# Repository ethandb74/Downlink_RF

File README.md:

# Downlink_RF
4-layer PCB LoRa Puck:

This is a usb powereed LoRA Transmitter made for long range comnmunication with a programmable OLED display. This project was built around the SX1262 Radio chip and the RP2040 microcontroller. 
This project is inteded to be used as an alternative to using esp32 wireless communcation protocol (ESPNOW). this provides longer range and a seperate module making it a workaround to (in my experience) an often unrealiable communcation protocol. I learned the basics of RF pcb desing with the ultimiate goal of understanding all the systems of a cubeSat. This Satlite subsystem focus inspired the name Downlink. 

This Trasmitter is a 4 layer PCB

:
-      Fcu - singal 
 -     In1.cu - GND plane (Earth)
  -     In3.cu- +3V3 power plane
   -     Bcu- secondary signal

Main power for the module is delived via USB-C

RF: traces are routed at 0.1756mm width for 50ohm impedance  and IPD handels most of the Frontend with the exception of a pi circuit 

Frequency and Band 
--
This Puck transmits at 915Mhz or the ISM band
This band is license free and causes no issue with the FCC 

Schematic
--
orginized into sections with power/ memeory/ RF/ Microcontoller/ 

PCB
--
4-layer traces are routed at 0.1756mm width for 50ohm impedance no right angles tight via fencing around the RF section 

Kepp in mind the photo above is before some final iterations This is a 3d model of the Finished PCB:

BOM:
Attached is a link to the BOM with the individual Componants for the PCB
[Bom Link](BOM/Downlink_RF.csv)

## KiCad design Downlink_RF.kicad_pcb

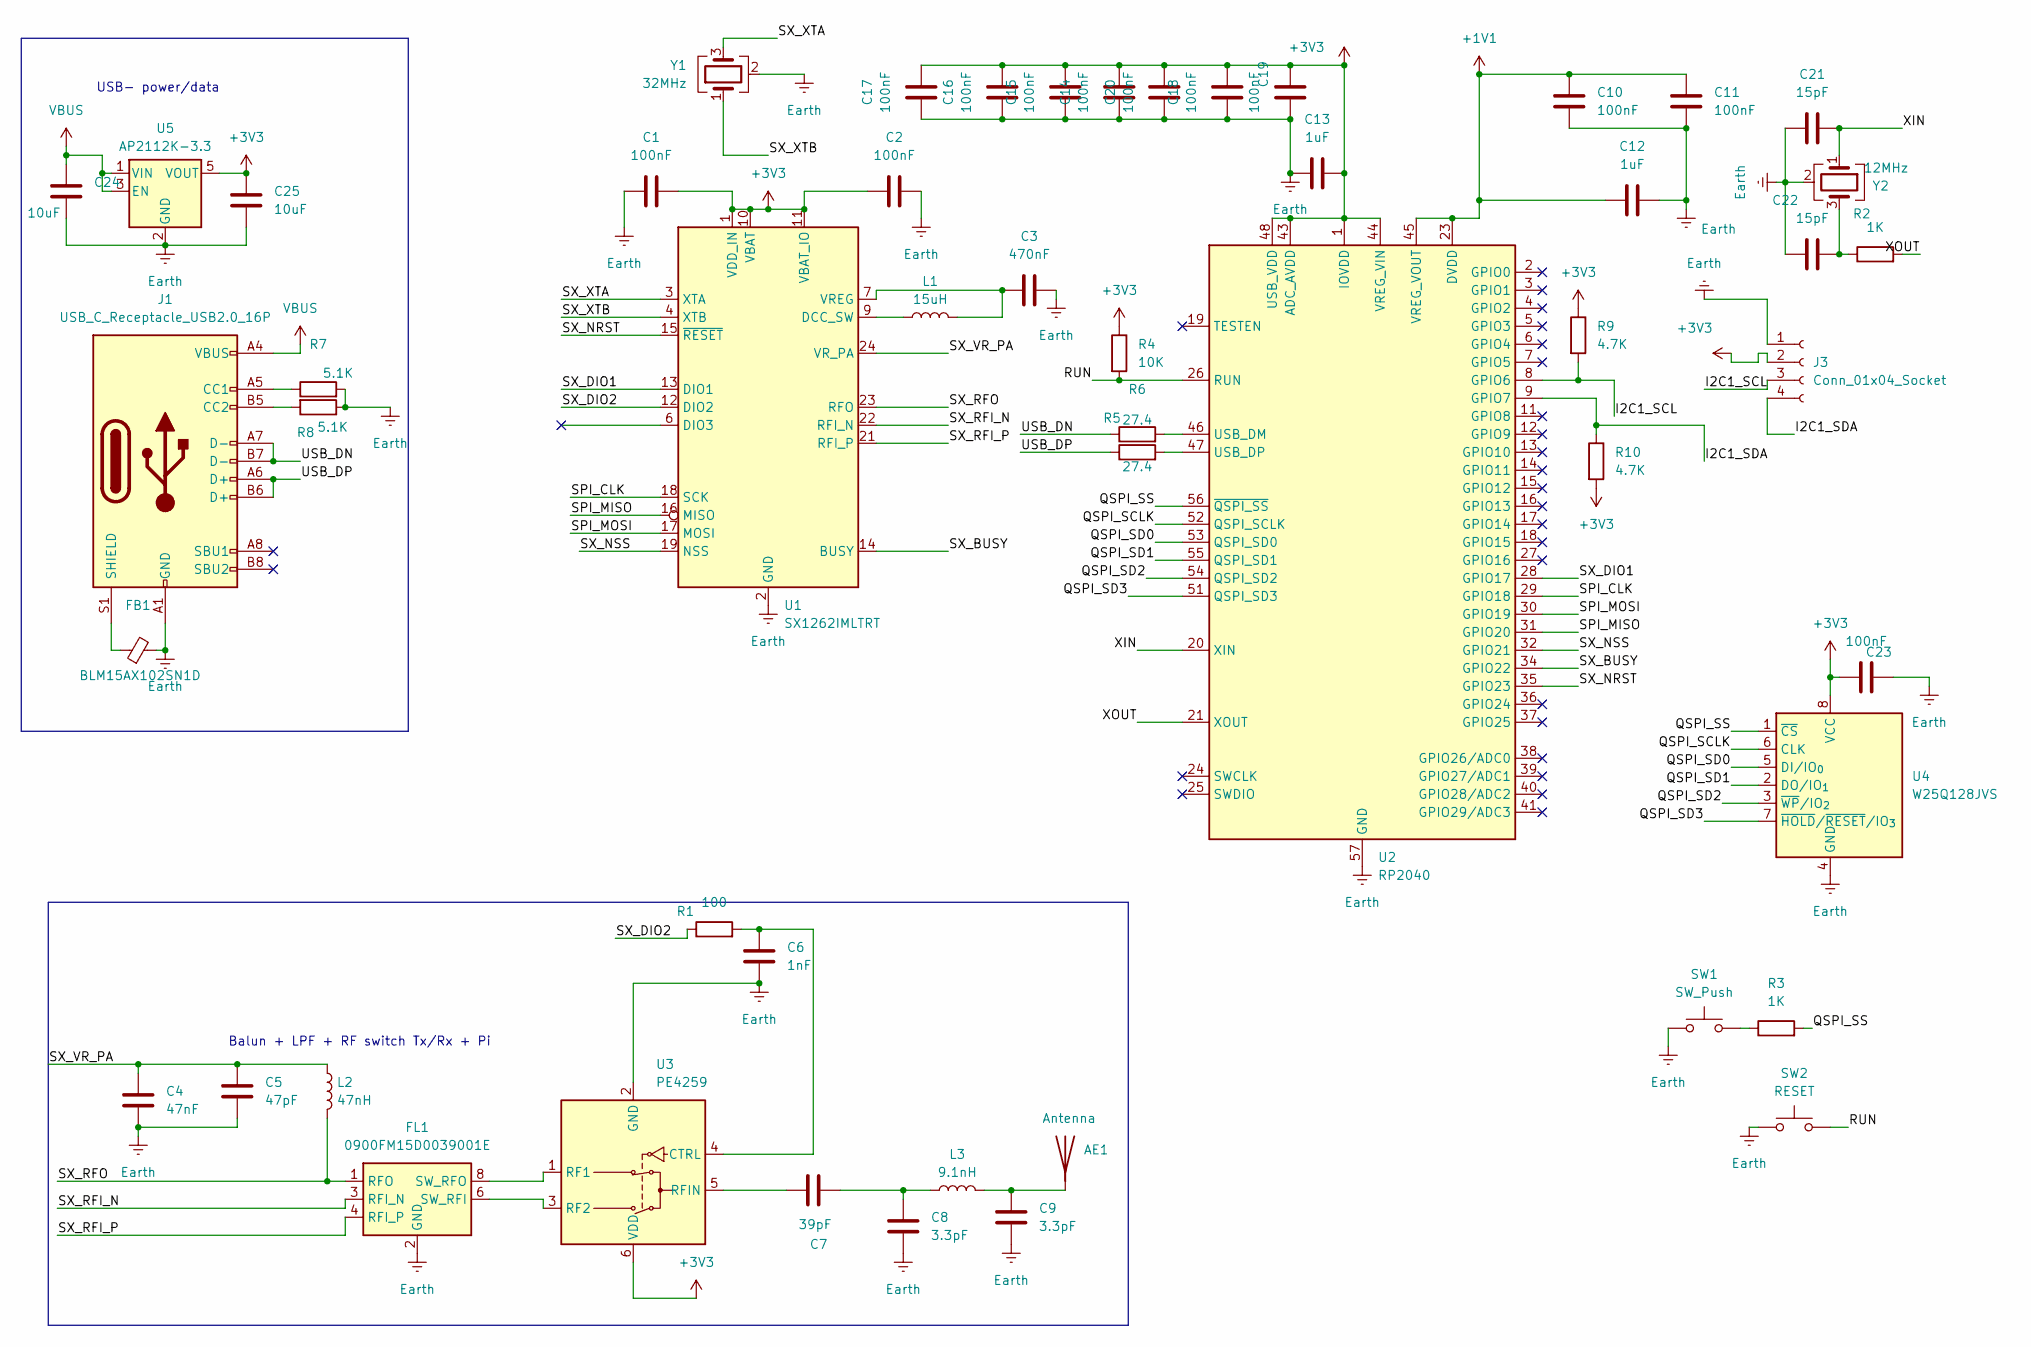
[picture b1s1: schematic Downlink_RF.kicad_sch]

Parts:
AE1: Antenna; PinSocket_1x01_P2.54mm_Vertical
C1, C2, C10, C11, C14, C15, C16, C17, C18, C19, C20, C23: 100nF; C_0402_1005Metric
C3: 470nF; C_0402_1005Metric
C4: 47nF; C_0402_1005Metric
C5: 47pF; C_0402_1005Metric
C6: 1nF; C_0402_1005Metric
C7: 39pF; C_0402_1005Metric
C8, C9: 3.3pF; C_0402_1005Metric
C12, C13: 1uF; C_0402_1005Metric
C21, C22: 15pF; C_0402_1005Metric
C24, C25: 10uF; C_0402_1005Metric
FB1: BLM15AX102SN1D; L_0402_1005Metric
FL1: 0900FM15D0039001E; Balun_Johanson_0900FM15K0039
J1: USB_C_Receptacle_USB2.0_16P; USB_C_Receptacle_GCT_USB4105-xx-A_16P_TopMnt_Horizontal
J3: Conn_01x04_Socket; PinSocket_1x04_P2.54mm_Vertical
L1: 15uH; L_0402_1005Metric
L2: 47nH; L_0402_1005Metric
L3: 9.1nH; L_0402_1005Metric
R1: 100; R_0402_1005Metric
R2, R3: 1K; R_0402_1005Metric
R4: 10K; R_0402_1005Metric
R5, R6: 27.4; R_0402_1005Metric
R7, R8: 5.1K; R_0402_1005Metric
R9, R10: 4.7K; R_0402_1005Metric
SW1: SW_Push; SW_Tactile_SPST_NO_Straight_CK_PTS636Sx25SMTRLFS
SW2: RESET; SW_Tactile_SPST_NO_Straight_CK_PTS636Sx25SMTRLFS
U1: SX1262IMLTRT; QFN-24-1EP_4x4mm_P0.5mm_EP2.6x2.6mm
U2: RP2040; QFN-56-1EP_7x7mm_P0.4mm_EP3.2x3.2mm
U3: PE4259; SOT-363_SC-70-6
U4: W25Q128JVS; SOIC-8_5.3x5.3mm_P1.27mm
U5: AP2112K-3.3; SOT-23-5
Y1: 32MHz; Crystal_SMD_3225-4Pin_3.2x2.5mm
Y2: 12MHz; Crystal_SMD_Abracon_ABM8G-4Pin_3.2x2.5mm

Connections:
+1V1: C10.2, C11.1, C12.2, U2.23 (DVDD), U2.45 (VREG_VOUT), U2.50 (DVDD)
+3V3: C1.2, C2.1, C13.2, C14.1, C15.1, C16.1, C17.1, C18.1, C19.1, C20.1, C23.1, C25.1, J3.2, R4.1, R9.1, R10.2, U1.1 (VDD_IN), U1.10 (VBAT), U1.11 (VBAT_IO), U2.1 (IOVDD), U2.10 (IOVDD), U2.22 (IOVDD), U2.33 (IOVDD), U2.42 (IOVDD), U2.43 (ADC_AVDD), U2.44 (VREG_VIN), U2.48 (USB_VDD), U2.49 (IOVDD), U3.6 (VDD), U4.8 (VCC), U5.5 (VOUT)
/I2C1_SCL: J3.3, R9.2, U2.8 (GPIO6)
/I2C1_SDA: J3.4, R10.1, U2.9 (GPIO7)
/QSPI_SCLK: U2.52 (QSPI_SCLK), U4.6 (CLK)
/QSPI_SD0: U2.53 (QSPI_SD0), U4.5 (DI/IO_{0})
/QSPI_SD1: U2.55 (QSPI_SD1), U4.2 (DO/IO_{1})
/QSPI_SD2: U2.54 (QSPI_SD2), U4.3 (~WP/IO_{2})
/QSPI_SD3: U2.51 (QSPI_SD3), U4.7 (~HOLD/~RESET/IO_{3})
/QSPI_SS: R3.2, U2.56 (~QSPI_SS), U4.1 (~CS)
/RUN: R4.2, SW2.2, U2.26 (RUN)
/SPI_CLK: U1.18 (SCK), U2.29 (GPIO18)
/SPI_MISO: U1.16 (MISO), U2.31 (GPIO20)
/SPI_MOSI: U1.17 (MOSI), U2.30 (GPIO19)
/SX_BUSY: U1.14 (BUSY), U2.34 (GPIO22)
/SX_DIO1: U1.13 (DIO1), U2.28 (GPIO17)
/SX_DIO2: R1.1, U1.12 (DIO2)
/SX_NRST: U1.15 (~RESET), U2.35 (GPIO23)
/SX_NSS: U1.19 (NSS), U2.32 (GPIO21)
/SX_RFI_N: FL1.3 (RFI_N), U1.22 (RFI_N)
/SX_RFI_P: FL1.4 (RFI_P), U1.21 (RFI_P)
/SX_RFO: FL1.1 (RFO), L2.2, U1.23 (RFO)
/SX_VR_PA: C4.1, C5.1, L2.1, U1.24 (VR_PA)
/SX_XTA: U1.3 (XTA), Y1.3
/SX_XTB: U1.4 (XTB), Y1.1
/USB_DN: J1.A7 (D-), J1.B7 (D-), R6.1
/USB_DP: J1.A6 (D+), J1.B6 (D+), R5.1
/XIN: C21.2, U2.20 (XIN), Y2.1
/XOUT: R2.2, U2.21 (XOUT)
Earth: C1.1, C2.2, C3.2, C4.2, C5.2, C6.2, C8.2, C9.2, C10.1, C11.2, C12.1, C13.1, C14.2, C15.2, C16.2, C17.2, C18.2, C19.2, C20.2, C21.1, C22.1, C23.2, C24.2, C25.2, FB1.2, FL1.2 (GND), FL1.5 (GND), FL1.7 (GND), FL1.9 (GND), FL1.10 (GND), J1.A1 (GND), J1.A12 (GND), J1.B1 (GND), J1.B12 (GND), J3.1, R7.2, R8.1, SW1.1, SW2.1, U1.2 (GND), U1.5 (GND), U1.8 (GND), U1.20 (GND), U1.25 (GND), U2.57 (GND), U3.2 (GND), U4.4 (GND), U5.2 (GND), Y1.2 (G), Y1.4 (G), Y2.2 (G), Y2.4 (G)
unnamed: AE1.1 (A), C9.1, L3.2
unnamed: C7.1, C8.1, L3.1
unnamed: C22.2, R2.1, Y2.3
unnamed: FL1.6 (SW_RFI), U3.3 (RF2)
unnamed: FL1.8 (SW_RFO), U3.1 (RF1)
unnamed: J1.A5 (CC1), R7.1
unnamed: J1.B5 (CC2), R8.2
unnamed: FB1.1, J1.S1 (SHIELD)
unnamed: R3.1, SW1.2
unnamed: L1.1, U1.9 (DCC_SW)
unnamed: C3.1, L1.2, U1.7 (VREG)
unnamed: R6.2, U2.46 (USB_DM)
unnamed: R5.2, U2.47 (USB_DP)
unnamed: C6.1, R1.2, U3.4 (CTRL)
unnamed: C7.2, U3.5 (RFIN)
VBUS: C24.1, J1.A4 (VBUS), J1.A9 (VBUS), J1.B4 (VBUS), J1.B9 (VBUS), U5.1 (VIN), U5.3 (EN)

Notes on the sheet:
Balun + LPF + RF switch Tx/Rx + Pi
USB- power/data

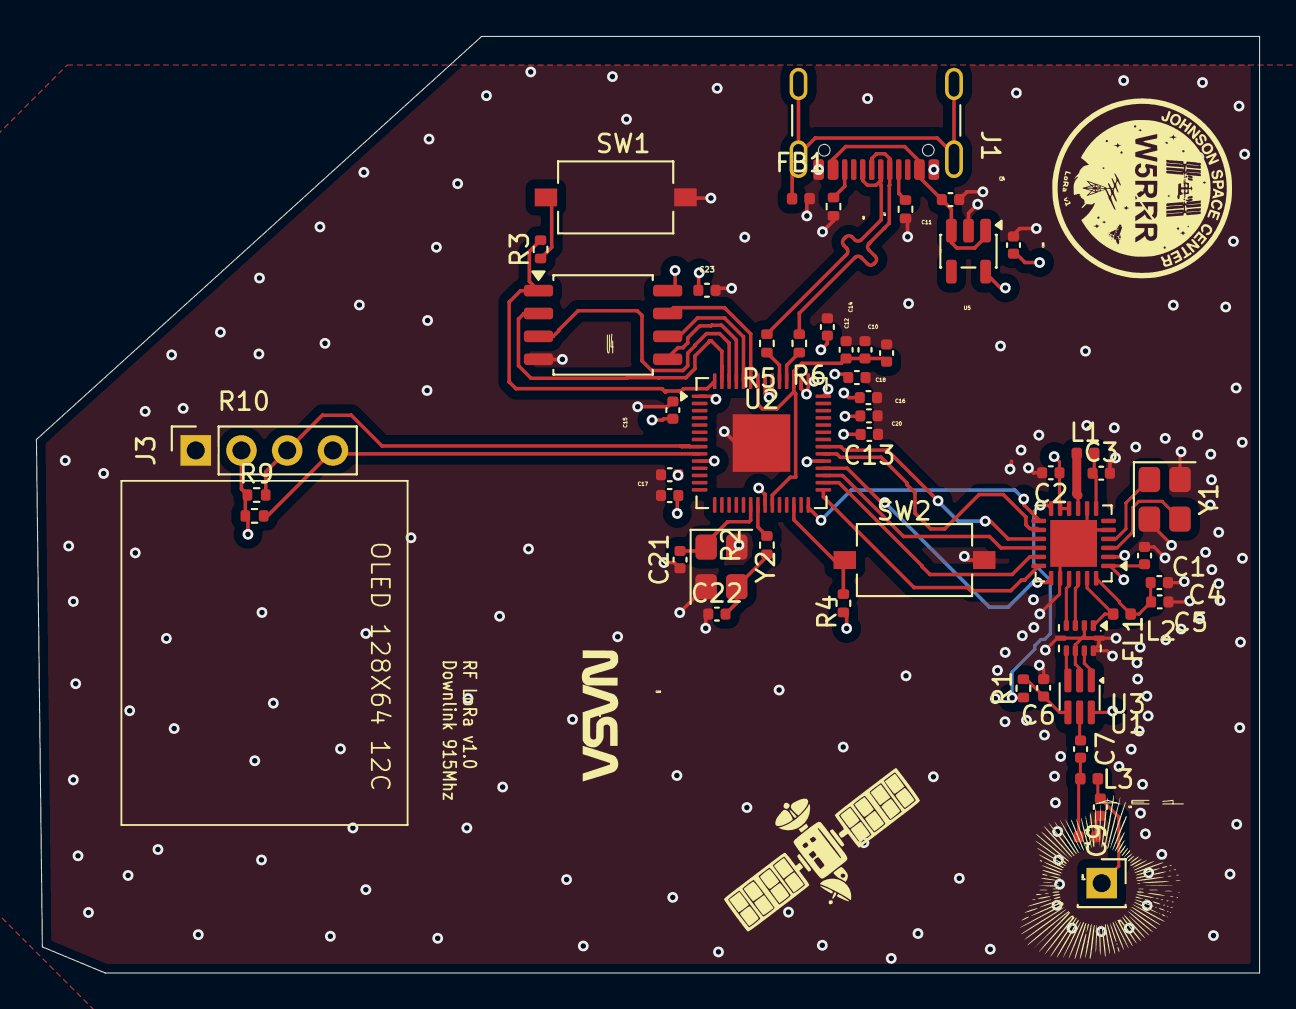
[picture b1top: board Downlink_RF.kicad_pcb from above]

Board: 4 copper layers, 67.9 x 52.0 mm, 53 parts (0 on the bottom side), 46 nets.

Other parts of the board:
G**: LOGO; satlogo2

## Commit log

2026-05-02 Update README.md
    not done yet
2026-05-03 Rename Downlink_RF.csv to BOM/Downlink_RF.csv
2026-05-03 Rename Downlink_RF.kicad_pcb to PCB/Downlink_RF.kicad_pcb
2026-05-03 Rename Downlink_RF.kicad_pro to PCB/Downlink_RF.kicad_pro
2026-05-03 Rename Downlink_RF.kicad_sch to Schematic/Downlink_RF.kicad_sch
2026-05-03 Rename Downlink_Gerbers.zip to Production/Downlink_Gerbers.zip
